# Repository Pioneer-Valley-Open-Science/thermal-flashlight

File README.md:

thermal-flashlight
==================

This is a design for [Public Lab](http://publiclab.org)'s [thermal flashlight](http://publiclab.org/wiki/thermal-camera), based on the awesome Rayshobby.net ["SquareWear" design](https://github.com/rayshobby/squarewear).  

### License

This design is released under the [CERN Open Hardware License](http://www.ohwr.org/attachments/2388/cern_ohl_v_1_2.txt)

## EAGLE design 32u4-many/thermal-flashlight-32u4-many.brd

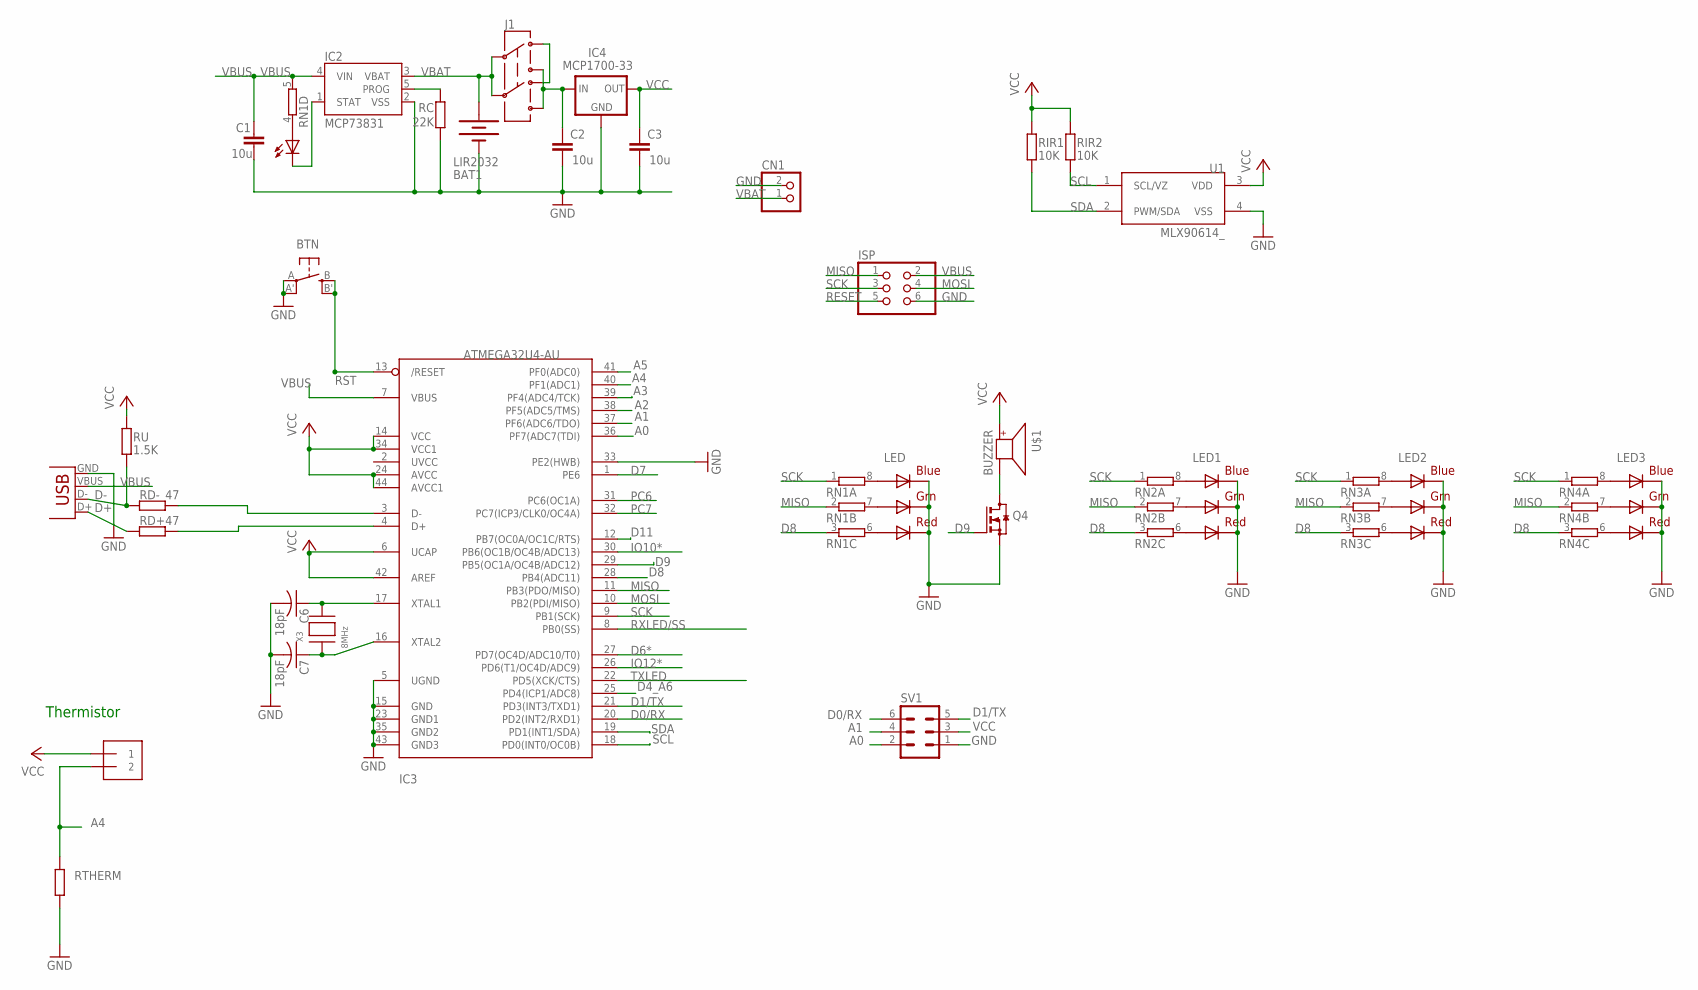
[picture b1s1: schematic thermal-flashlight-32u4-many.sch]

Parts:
BAT1: LIR2032; BATTCOM_20MM_PTH_SMT
BTN: EVQQ2; EVQ-Q2
C1, C2, C3: 10u; C0805
C6, C7: 18pF; C0805K
CHG: 0805; CHIPLED_0805
CN1: JST_2PIN-SMT-RA; JST-PH-2-SMT-RA
IC2: MCP73831; SOT23-5
IC3: ATMEGA32U4-AU; TQFP44
IC4: MCP1700-33; SOT23
ISP: PINHD-2X3; 2X03
J1: AYZ0202
J2: 1X2-3.5MM
LED, LED1, LED2, LED3: RGBLED5050
Q4: BSS123; SOT23
RC: 22K; R0805
RD+: 47; R0805
RD-: 47; R0805
RIR1, RIR2: 10K; R0805
RN1, RN2, RN3, RN4: 4R-NEXB38V; EXB38V
RTHERM: 330; 0204/7
RU: 1.5K; R0805
SV1: MA03-2
U1: MLX90614_; TO-39
U$1: BUZZER; SMT-8585-BUZZER
X1: USBSMD; USB-MINIB
X3: 8MHz; NX5032

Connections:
A0: IC3.36 (PF7(ADC7(TDI)), SV1.2
A1: IC3.37 (PF6(ADC6/TDO)), SV1.4
A2: IC3.38 (PF5(ADC5/TMS))
A3: IC3.39 (PF4(ADC4/TCK))
A4: IC3.40 (PF1(ADC1)), J2.2, RTHERM.2
A5: IC3.41 (PF0(ADC0))
D0/RX: IC3.20 (PD2(INT2/RXD1)), SV1.6
D1/TX: IC3.21 (PD3(INT3/TXD1)), SV1.5
D4_A6: IC3.25 (PD4(ICP1/ADC8))
D6*: IC3.27 (PD7(OC4D/ADC10/T0))
D7: IC3.1 (PE6)
D8: IC3.28 (PB4(ADC11)), RN1.3 (1), RN2.3 (1), RN3.3 (1), RN4.3 (1)
D9: IC3.29 (PB5(OC1A/OC4B/ADC12)), Q4.1 (G)
D11: IC3.12 (PB7(OC0A/OC1C/RTS))
D+: RD+.1, X1.D+
D-: RD-.1, RU.1, X1.D-
GND: BAT1.P$1 (-), BTN.A, BTN.A' (P1), C1.2, C2.2, C3.2, C6.2, C7.2, CN1.2 (1), IC2.2 (VSS), IC3.5 (UGND), IC3.15 (GND), IC3.23 (GND1), IC3.33 (PE2(HWB)), IC3.35 (GND2), IC3.43 (GND3), IC4.1 (GND), ISP.6, LED.4 (BLUE_C), LED.5 (RED_C), LED.6 (GREEN_C), LED1.4 (BLUE_C), LED1.5 (RED_C), LED1.6 (GREEN_C), LED2.4 (BLUE_C), LED2.5 (RED_C), LED2.6 (GREEN_C), LED3.4 (BLUE_C), LED3.5 (RED_C), LED3.6 (GREEN_C), Q4.2 (S), RC.1, RTHERM.1, SV1.1, U1.4 (VSS), X1.GND
IO10*: IC3.30 (PB6(OC1B/OC4B/ADC13))
IO12*: IC3.26 (PD6(T1/OC4D/ADC9))
MISO: IC3.11 (PB3(PDO/MISO)), ISP.1, RN1.2 (1), RN2.2 (1), RN3.2 (1), RN4.2 (1)
MOSI: IC3.10 (PB2(PDI/MISO)), ISP.4
unnamed: J1.3 (1), J1.6 (4)
unnamed: LED1.3 (BLUE_A), RN2.8 (2)
unnamed: LED1.1 (GREEN_A), RN2.7 (2)
unnamed: LED.3 (BLUE_A), RN1.8 (2)
unnamed: CHG.C, IC2.1 (STAT)
unnamed: IC2.5 (PROG), RC.2
unnamed: Q4.3 (D), U$1.-
unnamed: LED.1 (GREEN_A), RN1.7 (2)
unnamed: LED.2 (RED_A), RN1.6 (2)
unnamed: CHG.A, RN1.4 (1)
unnamed: IC3.4 (D+), RD+.2
unnamed: LED1.2 (RED_A), RN2.6 (2)
unnamed: LED2.3 (BLUE_A), RN3.8 (2)
unnamed: LED2.1 (GREEN_A), RN3.7 (2)
unnamed: C7.1, IC3.16 (XTAL2), X3.P$1
unnamed: C6.1, IC3.17 (XTAL1), X3.P$2
unnamed: LED2.2 (RED_A), RN3.6 (2)
unnamed: IC3.3 (D-), RD-.2
unnamed: LED3.3 (BLUE_A), RN4.8 (2)
unnamed: LED3.1 (GREEN_A), RN4.7 (2)
unnamed: LED3.2 (RED_A), RN4.6 (2)
PC6: IC3.31 (PC6(OC1A))
PC7: IC3.32 (PC7(ICP3/CLK0/OC4A))
RESET: ISP.5
RST: BTN.B (S), BTN.B' (S1), IC3.13 (/RESET)
RXLED/SS: IC3.8 (PB0(SS))
SCK: IC3.9 (PB1(SCK)), ISP.3, RN1.1, RN2.1, RN3.1, RN4.1
SCL: IC3.18 (PD0(INT0/OC0B)), RIR2.1, U1.1 (SCL/VZ)
SDA: IC3.19 (PD1(INT1/SDA)), RIR1.1, U1.2 (PWM/SDA)
TXLED: IC3.22 (PD5(XCK/CTS))
VBAT: BAT1.P$2 (+), CN1.1 (2), IC2.3 (VBAT), J1.2, J1.5
VBUS: C1.1, IC2.4 (VIN), IC3.7 (VBUS), ISP.2, RN1.5 (2), X1.VBUS
VCC: C3.1, IC3.6 (UCAP), IC3.14 (VCC), IC3.24 (AVCC), IC3.34 (VCC1), IC3.42 (AREF), IC3.44 (AVCC1), IC4.2 (OUT), J2.1, RIR1.2, RIR2.2, RU.2, SV1.3, U1.3 (VDD), U$1.+
VDD: C2.1, IC4.3 (IN), J1.1 (3), J1.4 (6)

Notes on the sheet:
Thermistor

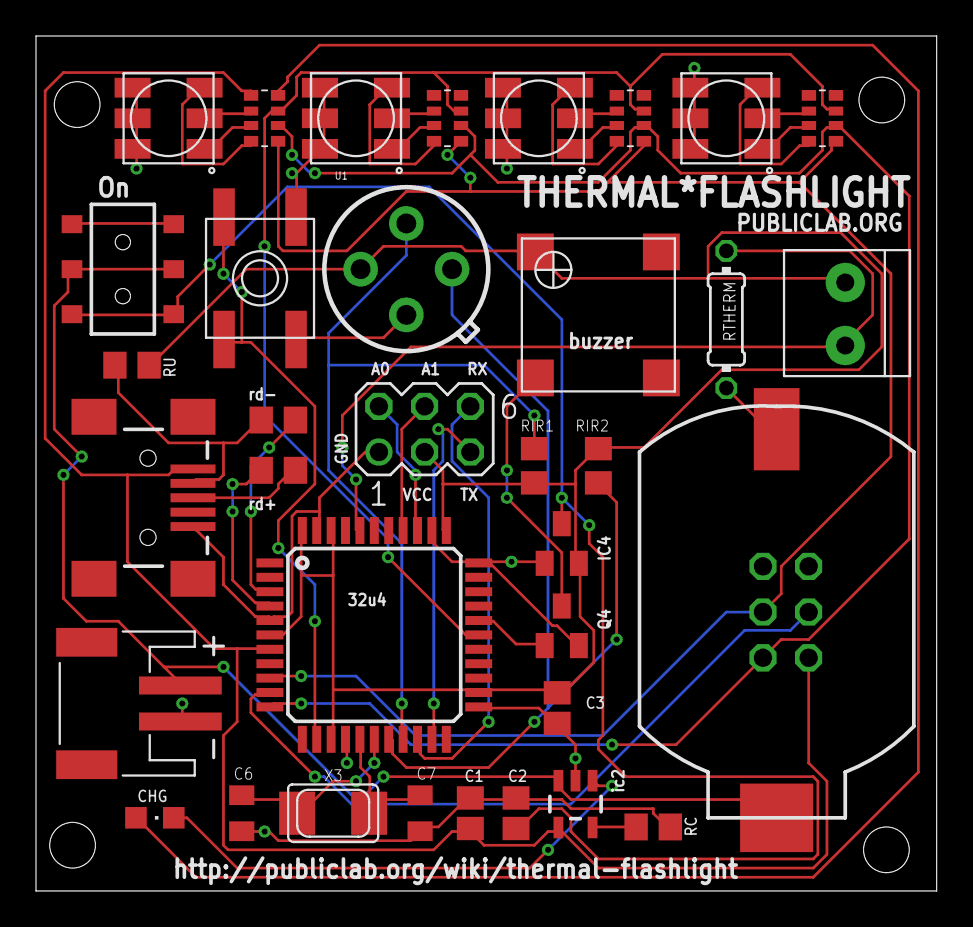
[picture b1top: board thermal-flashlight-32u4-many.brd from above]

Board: 2 copper layers, 50.0 x 47.5 mm, 36 parts (1 on the bottom side), 41 nets.

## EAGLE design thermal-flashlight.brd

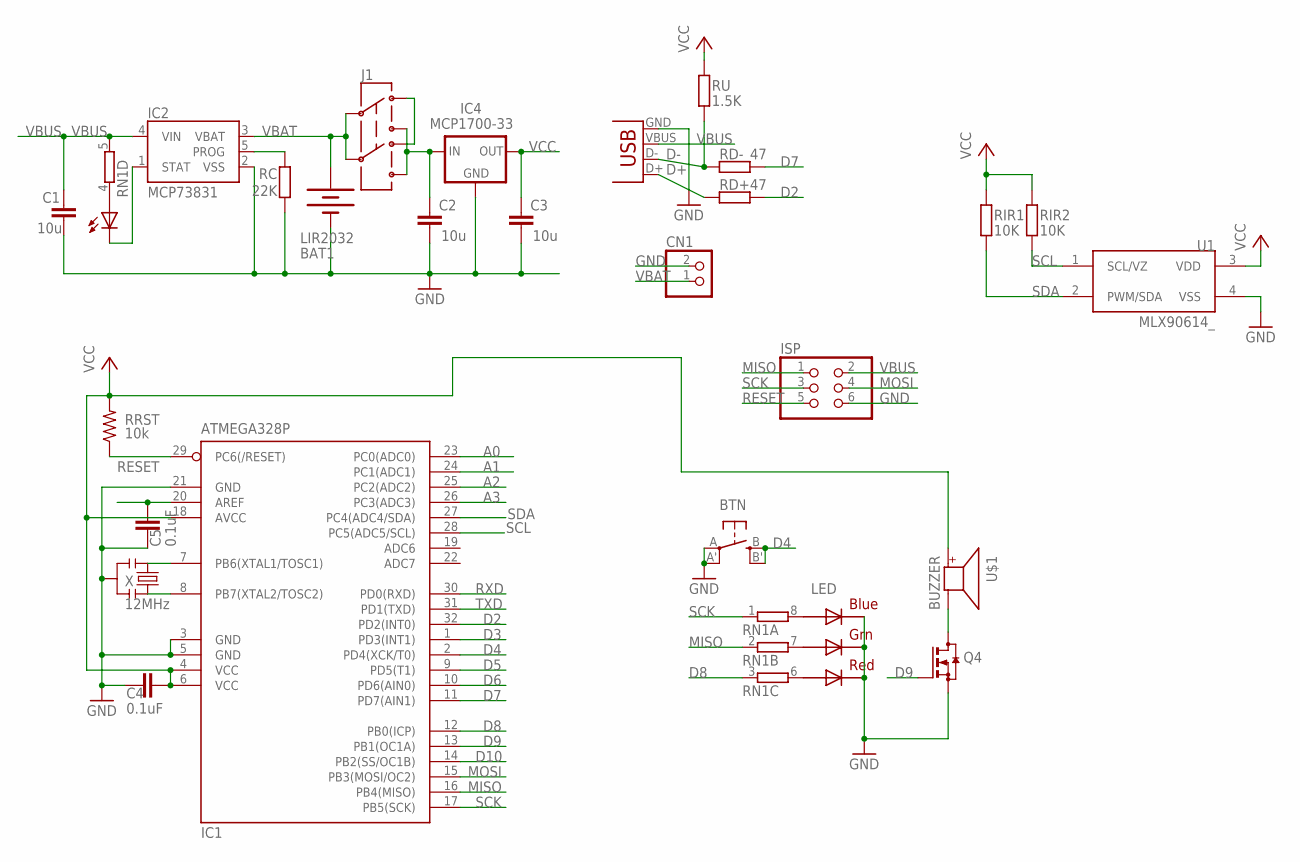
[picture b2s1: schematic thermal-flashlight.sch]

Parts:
BAT1: LIR2032; BATTCOM_20MM_PTH_SMT
BTN: EVQQ2; EVQ-Q2
C1, C2, C3: 10u; C0805
C4, C5: 0.1uF; C0805
CHG: 0805; CHIPLED_0805
CN1: JST_2PIN-SMT-RA; JST-PH-2-SMT-RA
IC1: ATMEGA328P; TQFP32-08
IC2: MCP73831; SOT23-5
IC4: MCP1700-33; SOT23
ISP: PINHD-2X3; 2X03
J1: AYZ0202
LED: RGBLED5050
Q4: BSS123; SOT23
RC: 22K; R0805
RD+: 47; R0805
RD-: 47; R0805
RIR1, RIR2: 10K; R0805
RN1: 4R-NEXB38V; EXB38V
RRST: 10k; R0805@1
RU: 1.5K; R0805
U1: MLX90614_; TO-39
U$1: BUZZER; SMT-8585-BUZZER
X: 12MHz; RESONATOR-SMD
X1: USBSMD; USB-MINIB

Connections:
A0: IC1.23 (PC0(ADC0)); also elsewhere on the board
A1: IC1.24 (PC1(ADC1)); also elsewhere on the board
A2: IC1.25 (PC2(ADC2)); also elsewhere on the board
A3: IC1.26 (PC3(ADC3))
AREF: C5.2, IC1.20 (AREF)
D2: IC1.32 (PD2(INT0)), RD+.2
D3: IC1.1 (PD3(INT1)); also elsewhere on the board
D4: BTN.B (S), BTN.B' (S1), IC1.2 (PD4(XCK/T0))
D5: IC1.9 (PD5(T1)); also elsewhere on the board
D6: IC1.10 (PD6(AIN0)); also elsewhere on the board
D7: IC1.11 (PD7(AIN1)), RD-.2
D8: IC1.12 (PB0(ICP)), RN1.3 (1)
D9: IC1.13 (PB1(OC1A)), Q4.1 (G)
D10: IC1.14 (PB2(SS/OC1B))
D+: RD+.1, X1.D+
D-: RD-.1, RU.1, X1.D-
GND: BAT1.P$1 (-), BTN.A, BTN.A' (P1), C1.2, C2.2, C3.2, C4.1, C5.1, CN1.2 (1), IC1.3 (GND), IC1.5 (GND), IC1.21 (GND), IC2.2 (VSS), IC4.1 (GND), ISP.6, LED.4 (BLUE_C), LED.5 (RED_C), LED.6 (GREEN_C), Q4.2 (S), RC.1, U1.4 (VSS), X.2, X1.GND; also elsewhere on the board
MISO: IC1.16 (PB4(MISO)), ISP.1, RN1.2 (1)
MOSI: IC1.15 (PB3(MOSI/OC2)), ISP.4
unnamed: J1.3 (1), J1.6 (4)
unnamed: IC1.7 (PB6(XTAL1/TOSC1)), X.1
unnamed: IC1.8 (PB7(XTAL2/TOSC2)), X.3
unnamed: LED.3 (BLUE_A), RN1.8 (2)
unnamed: CHG.C, IC2.1 (STAT)
unnamed: IC2.5 (PROG), RC.2
unnamed: Q4.3 (D), U$1.-
unnamed: LED.1 (GREEN_A), RN1.7 (2)
unnamed: LED.2 (RED_A), RN1.6 (2)
unnamed: CHG.A, RN1.4 (1)
RESET: IC1.29 (PC6(/RESET)), ISP.5, RRST.1
RXD: IC1.30 (PD0(RXD))
SCK: IC1.17 (PB5(SCK)), ISP.3, RN1.1
SCL: IC1.28 (PC5(ADC5/SCL)), RIR2.1, U1.1 (SCL/VZ); also elsewhere on the board
SDA: IC1.27 (PC4(ADC4/SDA)), RIR1.1, U1.2 (PWM/SDA); also elsewhere on the board
TXD: IC1.31 (PD1(TXD))
VBAT: BAT1.P$2 (+), CN1.1 (2), IC2.3 (VBAT), J1.2, J1.5
VBUS: C1.1, IC2.4 (VIN), ISP.2, RN1.5 (2), X1.VBUS
VCC: C3.1, C4.2, IC1.4 (VCC), IC1.6 (VCC), IC1.18 (AVCC), IC4.2 (OUT), RIR1.2, RIR2.2, RRST.2, RU.2, U1.3 (VDD), U$1.+; also elsewhere on the board
VDD: C2.1, IC4.3 (IN), J1.1 (3), J1.4 (6)

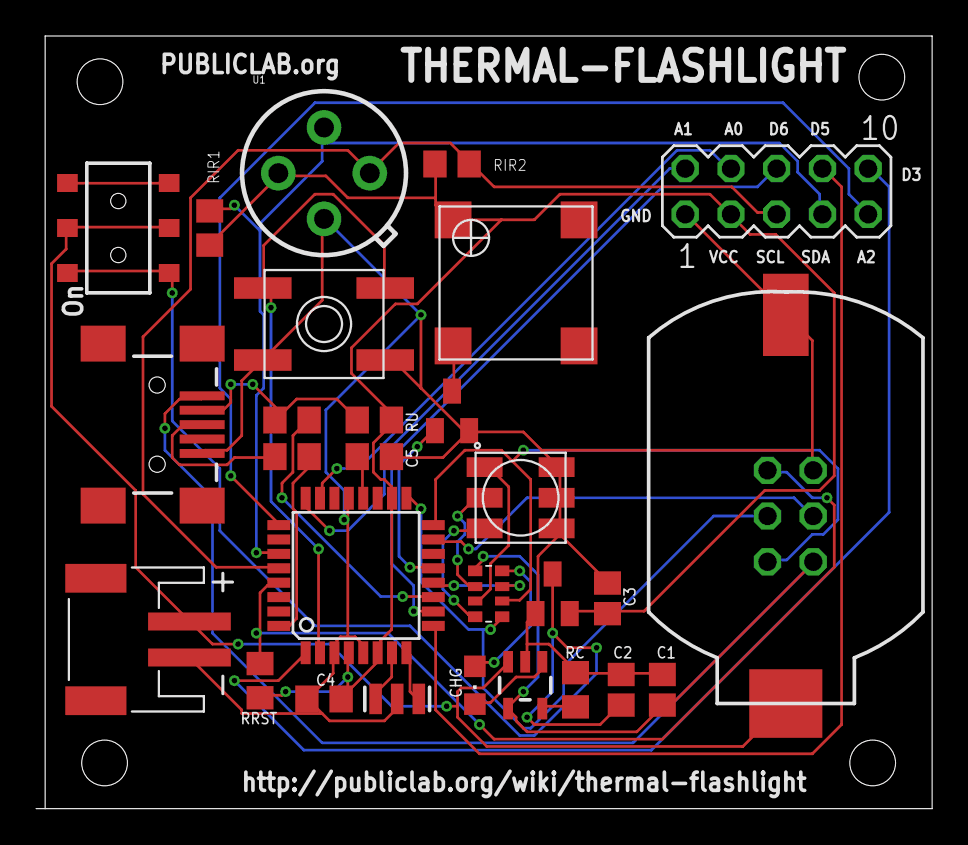
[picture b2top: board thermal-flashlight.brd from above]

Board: 2 copper layers, 49.8 x 42.9 mm, 29 parts (1 on the bottom side), 35 nets.

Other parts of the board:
SV1: MA05-2

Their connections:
A0: SV1.4; also elsewhere on the board
A1: SV1.2; also elsewhere on the board
A2: SV1.9; also elsewhere on the board
D3: SV1.10; also elsewhere on the board
D5: SV1.8; also elsewhere on the board
D6: SV1.6; also elsewhere on the board
GND: SV1.1; also elsewhere on the board
SCL: SV1.5; also elsewhere on the board
SDA: SV1.7; also elsewhere on the board
VCC: SV1.3; also elsewhere on the board

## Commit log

2014-01-26 added 32u4
